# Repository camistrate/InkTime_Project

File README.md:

# TSC-homework - Istrate Camelia-Elena 334CC
# InkTime Watch

## Block Diagram

## Bill of Materials (BOM)

The table below lists the main active components, connectors, and critical electromechanical parts used in the design. Standard passives, RF matching parts, and decoupling capacitors are included in the manufacturing BOM.

| Component / Module | Function | Package / Footprint | JLC / LCSC Part | Datasheet |
|---|---|---|---|---|
| **nRF52840-QIAA-R** | Main BLE MCU | aQFN73 (7x7) | [C190794](https://jlcpcb.com/partdetail/NordicSemicon-NRF52840_QIAAR/C190794) | [Nordic nRF52840 Product Specification](https://docs.nordicsemi.com/) |
| **BQ25180YBGR** | LiPo charger / power-path management | DSBGA-9 | [C3682423](https://jlcpcb.com/partdetail/TexasInstruments-BQ25180YBGR/C3682423) | [TI BQ25180 Datasheet](https://www.ti.com/lit/ds/symlink/bq25180.pdf) |
| **RT6160AWSC** | 3.3V buck-boost regulator | WLCSP-15 | [C7065276](https://jlcpcb.com/partdetail/Richtek_Tech-RT6160AWSC/C7065276) | [Richtek RT6160A Datasheet](https://www.richtek.com/assets/product_file/RT6160A/DS6160A-05.pdf) |
| **MAX17048G+T10** | 1-cell LiPo fuel gauge | DFN-8 (2x2) | [C2682616](https://jlcpcb.com/partdetail/AnalogDevices-MAX17048G_T10/C2682616) | [MAX17048 / MAX17049 Datasheet](https://www.analog.com/media/en/technical-documentation/data-sheets/MAX17048-MAX17049.pdf) |
| **BMA421** | IMU / motion sensing / step counter | LGA-12 (2x2) | [C5242966](https://jlcpcb.com/partdetail/Bosch_Sensortec-BMA421/C5242966) | [Bosch BMA421 Datasheet](https://www.bosch-sensortec.com/media/boschsensortec/downloads/datasheets/bst-bma421-ds004.pdf) |
| **DRV2605YZFR** | Haptic driver for ERM motor | VSSOP-10 / DSBGA-9 variant used in sources | [C81079](https://jlcpcb.com/partdetail/TexasInstruments-DRV2605YZFR/C81079) | [TI DRV2605 Datasheet](https://www.ti.com/cn/lit/ds/symlink/drv2605.pdf) |
| **2450AT18B100E** | 2.4 GHz chip antenna | SMD 3216 / 1206 class | [C5179427](https://jlcpcb.com/partdetail/Johanson_Technology-2450AT18B100E/C5179427) | [Johanson 2450AT18B100E Datasheet](https://www.johansontechnology.com/datasheets/2450AT18B100/2450AT18B100.pdf) |
| **USBLC6-2SC6Y** | USB ESD protection | SOT-23-6 | [C7519](https://jlcpcb.com/partdetail/Stmicroelectronics-USBLC6_2SC6Y/C7519) | [ST USBLC6-2 Datasheet](https://www.st.com/resource/en/datasheet/usblc6-2.pdf) |
| **KH-TYPE-C-16P** | USB Type-C connector | 16-pin SMD | [C2765186](https://jlcpcb.com/partdetail/Kinghelm-KH_TYPE_C_16P/C2765186) | [Kinghelm KH-TYPE-C-16P Datasheet](https://datasheet.lcsc.com/lcsc/2012121836_Kinghelm-KH-TYPE-C-16P_C2765186.pdf) |
| **503480-2400** | 24-pin 0.5 mm FPC connector for E-paper display | 24-pin FPC | [C2857168](https://jlcpcb.com/partdetail/Molex-5034802400/C2857160) | [Molex 503480-2400 Datasheet](https://www.molex.com/en-us/products/part-detail/5034802400) |
| **DMG2305UX** | P-channel MOSFET for E-paper power control | SOT-23 | [C2940629](https://jlcpcb.com/partdetail/TECHPUBLIC-DMG2305UX/C2940629) | [DMG2305UX Datasheet](https://www.diodes.com/assets/Datasheets/DMG2305UX.pdf) |
| **SI1308EDL-T1-GE3** | MOSFET used in display drive stage | SOT-23 | [C469327](https://jlcpcb.com/partdetail/VishayIntertech-SI1308EDL_T1GE3/C469327) | [SI1308EDL Datasheet](https://www.vishay.com/doc?63399) |
| **MBR0530** | Schottky diode used in E-paper pump circuit | SOD-123 | [C77336](https://jlcpcb.com/partdetail/78464-MBR0530/C77336) | [MBR0530 Datasheet](https://www.onsemi.com/pdf/datasheet/mbr0530t1-d.pdf) |
| **EVP-AKE31A / tactile switch** | User input buttons | SMD tactile | [C2845028](https://jlcpcb.com/partdetail/Panasonic-EVP_AKE31A/C2845028) | [Panasonic Tactile Switch Datasheet](https://industrial.panasonic.com/cdbs/www-data/pdf/ATV0000/ATV0000CE3.pdf) |
| **LCM1027B3605F** | Vibration motor | Wire leads | [C7528806](https://jlcpcb.com/partdetail/7528806-LCM1027B3605F/C7528806) | [LCM1027B3605F Datasheet](https://datasheet.lcsc.com/lcsc/2310131633_LCM-LCM1027B3605F_C7528806.pdf) |
| **TC2030-IDC** | SWD programming / debug interface | Tag-Connect 6-pin footprint | [Tag-Connect Product Page](https://www.tag-connect.com/product/tc2030-idc-nl) | [TC2030 Documentation](https://www.tag-connect.com/product/tc2030-idc-6-pin-tag-connect-plug-of-nails-spring-pin-cable-with-ribbon-connector) |
| **32 MHz Crystal** | Main high-frequency crystal for nRF52840 | 2016 | [C5265841](https://jlcpcb.com/partdetail/Huiyuancrystal-HY32MSMD2016CA1R30/C5265841) | [32 MHz Crystal Datasheet](https://www.lcsc.com/product-detail/C7275071.html) |
| **32.768 kHz Crystal** | Low-frequency RTC crystal | 3215 | [C70509](https://jlcpcb.com/partdetail/NDK-NX3215SA_32_768KHZ_EXS00AMU00466/C70509) | [32.768 kHz Crystal Datasheet](https://ro.mouser.com/ProductDetail/NDK/NX3215SA-32.768K-STD-MUS-2) |
| **E-Paper Display 1.54 inch** | Main display module | 24-pin FPC | [C359944](https://jlcpcb.com/partdetail/Waveshare-4_2inch_e_PaperModule/C359944) | [WSH-12561 Datasheet](https://www.tme.eu/Document/0ca57a8ffbcd57b5bca53252eb9d6ec3/WSH-12561.pdf) |
| **LiPo Battery 250 mAh** | Main energy storage | Battery pack | - | [AKY0106 Datasheet](https://www.tme.eu/Document/b9e12bf26ad0ba929a22ab5d58f022cd/AKY0106.pdf) |

## Hardware Description

### MCU - nRF52840

The **nRF52840** is the central processing unit of the system. It integrates:

* ARM Cortex-M4F running at 64 MHz with FPU
* Bluetooth Low Energy (BLE 5.0)
* USB 2.0 Full Speed interface
* 1 MB Flash / 256 KB RAM

All major peripherals are connected directly to the nRF52840 through SPI, I2C, and GPIO interfaces.

---

## Power Path

```text
USB-C --> BQ25180 (charger) --> LiPo battery
                             --> VSYS
VSYS --> RT6160 (buck-boost) --> 3.3V rail (VDD_3V3)
```

### BQ25180

The **BQ25180** is used as the battery charger and power-path management IC. It:

* charges the LiPo battery
* provides the system rail (VSYS)
* communicates with the MCU over I2C
* raises an interrupt for charger or fault events

### RT6160

The **RT6160** is the main buck-boost regulator. It converts VSYS to a stable **3.3V rail**, which powers:

* the nRF52840
* the sensors
* the display logic
* the haptic driver

### MAX17048

The **MAX17048** is used as a fuel gauge. It monitors battery voltage and state of charge and communicates with the MCU over I2C. It also provides an **ALERT** signal for low-battery or battery-status events.

---

## E-Paper Display

The e-paper display is controlled through SPI and additional GPIO control signals.

| Signal   | Direction     | Description           |
| -------- | ------------- | --------------------- |
| SCK      | MCU → Display | SPI clock             |
| MOSI     | MCU → Display | SPI data              |
| EPD_CS   | MCU → Display | Chip select           |
| EPD_DC   | MCU → Display | Data / Command select |
| EPD_RST  | MCU → Display | Display reset         |
| EPD_BUSY | Display → MCU | Busy/status signal    |

The display power circuit includes:

* inductors
* Schottky diodes
* MOSFET switching elements

This stage generates the voltages required by the e-paper panel, such as **PREVGH** and **PREVGL**.

---

## IMU - BMA421

The **BMA421** is the motion sensor used in the design.

* Interface: **I2C**
* Functions:

  * acceleration sensing
  * motion detection
  * step-related events
* Interrupt outputs:

  * **INT1**
  * **INT2**

---

## Haptic Driver - DRV2605

The **DRV2605** is used to drive the vibration motor.

* Interface: **I2C**
* Enable signal: **HAPTIC_EN**
* Function: haptic feedback generation

---

## USB Interface

The board uses a **USB Type-C connector** together with an **USBLC6-2SC6Y** ESD protection device.

Signals:

* **VBUS**
* **D+**
* **D-**

This interface is used for:

* charging input
* USB detection by the MCU

---

## RF and Antenna

A **2450AT18B100E 2.4 GHz chip antenna** is connected to the RF output of the nRF52840.

The RF section includes:

* matching network components
* antenna keepout area
* no copper/traces under the antenna region

---

## User Interface

The design includes three push buttons:

* Up
* Down
* Enter / Esc

These are connected to GPIO pins of the MCU and used as active-low digital inputs.

---

## Debug Interface

Programming and debugging are performed through the **TC2030 SWD interface**, using:

* SWDIO
* SWDCLK
* RESET
* SWO
* 3.3V
* GND

---

## nRF52840 Pin Mapping

### Shared I2C Bus

* **P0.06** - SDA
  Used for communication with:

  * BMA421
  * MAX17048
  * BQ25180
  * RT6160
  * DRV2605

* **P0.07** - SCL
  Shared I2C clock line for all I2C peripherals

### SPI Bus (E-Paper Display)

* **P0.02** - SCK
* **P0.03** - MOSI
* **P0.05** - EPD_CS
* **P0.15** - EPD_DC
* **P0.16** - EPD_RST
* **P0.17** - EPD_BUSY

### Display Power Control

* **P1.01** - PFET gate control for display power enable

### Interrupts and Peripheral Control

* **P0.08** - BMA421 INT1
* **P1.08** - BMA421 INT2
* **P0.10** - MAX17048 ALERT
* **P0.11** - BQ25180 PMIC interrupt
* **P0.12** - DRV2605 enable

### Buttons

* **P0.13** - Up button
* **P0.14** - Down button
* **P1.00** - Enter / Esc button

### USB

* **D+** - USB data positive
* **D-** - USB data negative
* **VBUS** - USB power detection

### RF

* **ANT** - connected to the 2.4 GHz antenna through the matching network

### Debug and Clocks

* **SWDIO** - debug data
* **SWDCLK** - debug clock
* **RESET** - hardware reset
* **SWO** - debug trace output
* **XC1 / XC2** - 32 MHz crystal
* **XL1 / XL2** - 32.768 kHz crystal

---

## Design Rationale for Pin Selection

The selected pins were chosen to:

* use dedicated hardware interfaces for I2C and SPI
* keep related signals grouped logically
* simplify PCB routing
* support interrupt-driven operation for low-power behavior
* provide a clean debug and programming interface

---

## Power Consumption Considerations

The hardware is designed for low-power operation:

* **nRF52840** supports sleep and low-power modes
* **E-paper display** only consumes significant power during refresh
* **BMA421** is a low-power motion sensor
* **DRV2605 + motor** draw higher current only during short haptic events

Power efficiency is improved by:

* enabling only the peripherals that are needed
* using a regulated 3.3V rail
* controlling display-related power stages separately

## PCB Top View

## 3D PCB Render

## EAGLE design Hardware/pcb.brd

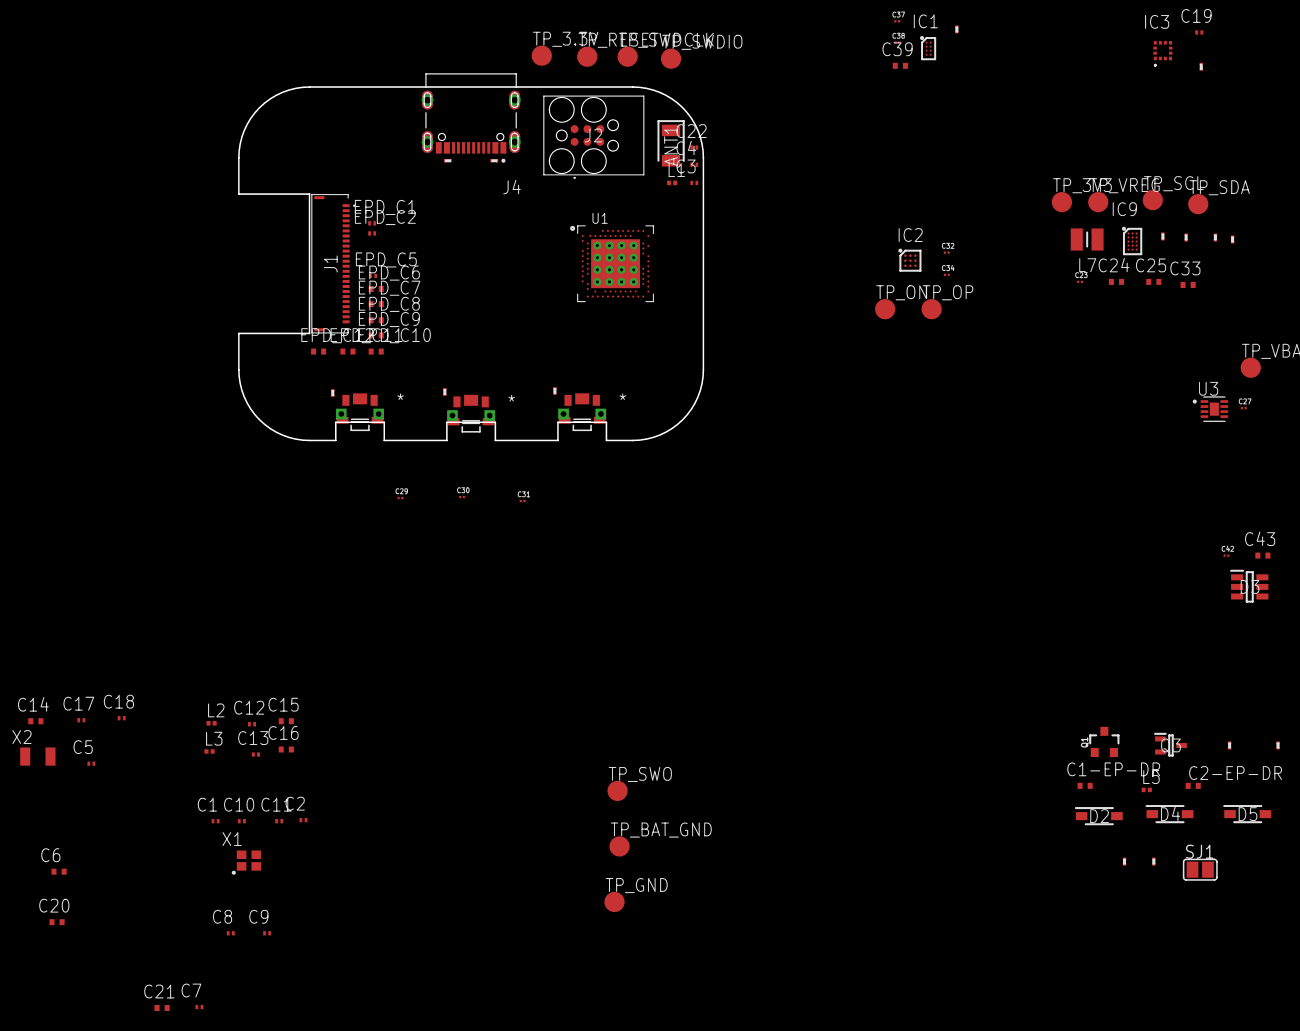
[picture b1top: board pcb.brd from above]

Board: 4 copper layers, 46.0 x 35.0 mm, 105 parts (0 on the bottom side), 75 nets, no tracks yet.

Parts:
ANT1: 2450AT18B100E; 2450AT18B100E_ANTC3216X140N
C1, C2, C17, C18: 12pF; NORDIC_NRF_3_RESC0201_L
C1-EP-DR, C24, C39: 10uF; NORDIC_NRF_3_RESC0402_L
C2-EP-DR: 4.7uF/25V; NORDIC_NRF_3_RESC0402_L
C3, C4: 1pF; NORDIC_NRF_3_RESC0201_L
C5, C7, C8, C12, C19: 100nF; NORDIC_NRF_3_RESC0201_L
C6, C14, C20, C21: 4.7µF; NORDIC_NRF_3_RESC0402_L
C9: 820pF; NORDIC_NRF_3_RESC0201_L
C10, C13, C22: N.C.; NORDIC_NRF_3_RESC0201_L
C11: 100pF; NORDIC_NRF_3_RESC0201_L
C15: 1.0µF; NORDIC_NRF_3_RESC0402_L
C16: 47µF; NORDIC_NRF_3_RESC0402_L
C23, C27, C34, C42: 0.1uF; GRM011R60J152KE01L_2_CAPC0201X13N
C25, C33: 22uF; NORDIC_NRF_3_RESC0402_L
C29, C30, C31, C32, C37, C38: 1uF; GRM011R60J152KE01L_2_CAPC0201X13N
C43: 4.7uF; NORDIC_NRF_3_RESC0402_L
D2, D4, D5: MBR0530; ESP32_C6_LIBRARY_5_SOD3716X135N
D3: USBLC6-2SC6Y; ESP32_C6_LIBRARY_3_SOT95P280X145-6N
EPD_C1, EPD_C2: 1uF/50V; NORDIC_NRF_3_RESC0201_L
EPD_C5: 0.1uF/50V; NORDIC_NRF_3_RESC0201_L
EPD_C6, EPD_C7, EPD_C8, EPD_C9, EPD_C10, EPD_C11, EPD_C12: 1uF/50V; NORDIC_NRF_3_RESC0402_L
IC1: BQ25180YBGR; BQ25180YBGR_BGA8C40P2X4_100X155X50
IC2: DRV2605YZFR; DRV2605YZFR_BGA9C50P3X3_144X144X62
IC3: BMA423; BMA423_BMA423
IC9: RT6160AWSC; RT6160AWSC_BGA15C40P3X5_140X230X60
J1: 503480-2400; 503480-2400_5034802400
J2: TC2030-IDC; TC2030-IDC_TC2030IDC
J4: KH-TYPE-C-16P; KH-TYPE-C-16P_KINGHELM_KH-TYPE-C-16P
L1: 3.9nH; NORDIC_NRF_2_RESC0201_N
L2: 10µH; NORDIC_NRF_2_RESC0201_N
L3: 15µH; NORDIC_NRF_2_RESC0201_N
L5: 68uH; NORDIC_NRF_2_RESC0201_N
L7: FTC252012SR47MBCA; MLP2016SR47MT0S1_INDC2016X100N
Q1: 20V/4.2A/52mΩ/1.4W; ESP32_C6_LIBRARY_4_ESP32_C6_LIBRARY_4_ESP32_C6_LIBRARY_4_ES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
Q3: SI1308EDL-T1-GE3; ESP32_C6_LIBRARY_6_SOT65P210X110-3N
R1_EP_DR: 0.47; CPF0201D7K68C1_0201
R1_USB, R2_USB: 5k1; ERA-1AEB3401C_0201
R2, R4: 0; CPF0201D7K68C1_0201
R2_EP_DR: 10K; CPF0201D7K68C1_0201
R3: 0; ERA-1AEB3401C_0201
R5, R7, R8, R9: 10k; CPF0201D7K68C1_0201
R17, R18: 3K3; ERA-1AEB3401C_0201
R_PWR_EPD: 10K; CPF0201D7K68C1_0201
R_TYPE_SEL: 2.2; CPF0201D7K68C1_0201
SJ1: ESP32_C6_LIBRARY_7_JUMPER_SJ
SW_DN: 2025-10-22_07-23-44_LIBRARY_EVP-AKE31ASW_EVP-AKE3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; 2025-10-22_07-23-44_LIBRARY_SW_EVP-AKE31A_PAN
SW_ENT: 2025-10-22_07-23-44_LIBRARY_EVP-AKE31ASW_EVP-AKE3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; 2025-10-22_07-23-44_LIBRARY_SW_EVP-AKE31A_PAN
SW_UP: 2025-10-22_07-23-44_LIBRARY_EVP-AKE31ASW_EVP-AKE3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; 2025-10-22_07-23-44_LIBRARY_SW_EVP-AKE31A_PAN
TP_3.3V, TP_3V3: HECTOR_WATCH_1_TPTP20R; HECTOR_WATCH_1_TP20R
TP_BAT_GND: HECTOR_WATCH_1_TPTP20R; HECTOR_WATCH_1_TP20R
TP_GND: HECTOR_WATCH_1_TPTP20R; HECTOR_WATCH_1_TP20R
TP_ON: HECTOR_WATCH_1_TPTP20R; HECTOR_WATCH_1_TP20R
TP_OP: HECTOR_WATCH_1_TPTP20R; HECTOR_WATCH_1_TP20R
TP_RESET: HECTOR_WATCH_1_TPTP20R; HECTOR_WATCH_1_TP20R
TP_SCL: HECTOR_WATCH_1_TPTP20R; HECTOR_WATCH_1_TP20R
TP_SDA: HECTOR_WATCH_1_TPTP20R; HECTOR_WATCH_1_TP20R
TP_SWDCLK: HECTOR_WATCH_1_TPTP20R; HECTOR_WATCH_1_TP20R
TP_SWDIO: HECTOR_WATCH_1_TPTP20R; HECTOR_WATCH_1_TP20R
TP_SWO: HECTOR_WATCH_1_TPTP20R; HECTOR_WATCH_1_TP20R
TP_VBAT: HECTOR_WATCH_1_TPTP20R; HECTOR_WATCH_1_TP20R
TP_VREG: HECTOR_WATCH_1_TPTP20R; HECTOR_WATCH_1_TP20R
U1: NRF52840_QF; NORDIC_NRF_4_AQFN50P700X700X85_HS-74N
U3: MAX17048G+T10; ESP32_C6_LIBRARY_SON50P200X200X80-9N
X1: 32MHz; NORDIC_NRF_BT-XTAL_2016_N
X2: 32.768kHz; NORDIC_NRF_1_XTAL_3215_N

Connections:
3V3/1.7D: C34.2, IC2.C2, Q1.2, R5.2, R_PWR_EPD.2
3V3/2.4A: C6.1, C7.1, C8.1, C12.1, C14.1, C19.1, C25.1, C33.1, IC3.3, IC3.7, IC3.10, IC9.E2, IC9.E3, J2.1, R17.1, R18.1, TP_3.3V.TP, TP_3V3.TP, U1.P$A22, U1.P$AD14, U1.P$AD23, U1.P$B1, U1.P$W1, U1.P$Y2
ALERT: U1.P$J24, U3.5
D+: D3.4, U1.P$AD6
D-: D3.6, U1.P$AD4
DEC1: C5.1, U1.P$C1
DEC3: C11.1, U1.P$D23
DEC4_6: C10.1, C15.1, C16.1, L3.2, U1.P$B5, U1.P$E24
DN: D3.1, J4.A7, J4.B7
DP: D3.3, J4.A6, J4.B6
EPD_3V3: C1-EP-DR.1, EPD_C5.2, J1.15, J1.16, L5.1, Q1.3
EPD_BUSY: J1.9, U1.P$AD12
EPD_CS: J1.12, U1.P$K2
EPD_DC: J1.11, U1.P$AD10
EPD_RST: J1.10, U1.P$AC11
GDR: J1.2, Q3.1, R2_EP_DR.2
GND: C1.2, C1-EP-DR.2, C2.2, C3.2, C4.2, C5.2, C6.2, C7.2, C8.2, C9.2, C10.2, C11.2, C12.2, C13.2, C14.2, C15.2, C16.2, C17.1, C18.1, C19.2, C20.2, C21.2, C22.2, C23.2, C24.1, C25.2, C27.1, C29.1, C30.1, C31.1, C32.1, C33.2, C34.1, C37.1, C38.1, C39.2, C42.2, C43.2, D3.2, D4.1, EPD_C1.1, EPD_C2.1, EPD_C5.1, EPD_C6.1, EPD_C7.1, EPD_C8.1, EPD_C9.1, EPD_C10.1, EPD_C11.1, EPD_C12.1, IC1.D2, IC2.B1, IC2.B3, IC3.8, IC3.9, IC9.B1, IC9.C1, IC9.C2, IC9.C3, J1.8, J1.17, J1.MP1, J1.MP2, J2.3, J2.5, J4.A1_B12, J4.A12_B1, J4.SH1, J4.SH2, J4.SH3, J4.SH4, R1_USB.1, R2_EP_DR.1, R2_USB.2, R3.1, R9.1, R_TYPE_SEL.1, SJ1.1, SW_DN.1, SW_ENT.1, SW_UP.1, TP_BAT_GND.TP, TP_GND.TP, U1.P$74, U1.P$75, U1.P$76, U1.P$77, U1.P$78, U1.P$79, U1.P$80, U1.P$81, U1.P$82, U1.P$83, U1.P$84, U1.P$85, U1.P$86, U1.P$87, U1.P$88, U1.P$89, U1.P$90, U1.P$B7, U1.P$F23, U3.1, U3.4, U3.6, U3.9, X1.2, X1.4
HAPTIC_EN: IC2.A1, U1.P$U1
IMU_INT1: IC3.5, U1.P$N1
IMU_INT2: IC3.6, U1.P$P2
LX1: IC9.B2, IC9.B3, L7.1
LX2: IC9.D2, IC9.D3, L7.2
MOSI: J1.14, U1.P$B13
unnamed: EPD_C7.2, J1.19
unnamed: IC9.D1, R4.2
unnamed: IC1.D1, R9.2
unnamed: C20.1, U1.P$AC5
unnamed: IC9.E1, R2.2
unnamed: IC3.1, R3.2
unnamed: C2-EP-DR.1, D2.1, D4.2
unnamed: C2-EP-DR.2, D5.2, L5.2, Q3.3
unnamed: R1_EP_DR.1, R_TYPE_SEL.2, SJ1.2
unnamed: L2.1, U1.P$B3
unnamed: L2.2, L3.1
unnamed: C13.1, U1.P$A18
unnamed: C9.1, U1.P$N24
unnamed: C2.1, U1.P$A23, X1.3
unnamed: C3.1, L1.1, U1.P$H23
unnamed: C1.1, U1.P$B24, X1.1
unnamed: EPD_C2.2, J1.4
unnamed: EPD_C1.2, J1.5
unnamed: EPD_C12.2, J1.24
unnamed: EPD_C8.2, J1.20
unnamed: EPD_C10.2, J1.22
unnamed: EPD_C6.2, J1.18
unnamed: C32.2, IC2.A2
unnamed: J4.B5, R2_USB.1
unnamed: J4.A5, R1_USB.2
OUT+: IC2.A3, TP_OP.TP
OUT-: IC2.C3, TP_ON.TP
P0.00/XL1: C17.2, U1.P$D2, X2.1
P0.01/XL2: C18.2, U1.P$F2, X2.2
P0.13: C30.2, R5.1, SW_UP.2, U1.P$AD8
P0.14: C31.2, R8.1, SW_ENT.2, U1.P$AC9
P1.01: Q1.1, R_PWR_EPD.1, U1.P$Y23
P1.02: C29.2, R7.1, SW_DN.2, U1.P$W24
PMIC_INT: IC1.A1, U1.P$T2
PREVGH: D5.1, EPD_C9.2, J1.21
PREVGL: D2.2, EPD_C11.2, J1.23
RESE: J1.3, Q3.2, R1_EP_DR.2
RESET: J2.6, TP_RESET.TP, U1.P$AC13
RF: ANT1.1, C4.1, C22.1, L1.2
SCK: J1.13, U1.P$A12
SCL/1.4C: IC2.C1, U3.7
SCL/2.4C: IC1.B1, IC3.12, R4.1, R17.2, TP_SCL.TP, U1.P$M2
SDA/1.4C: IC2.B2, U3.8
SDA/2.4C: IC1.C1, IC3.2, R2.1, R18.2, TP_SDA.TP, U1.P$L1
SWDCLK: J2.4, TP_SWDCLK.TP, U1.P$AA24
SWDIO: J2.2, TP_SWDIO.TP, U1.P$AC24
SWO: TP_SWO.TP, U1.P$AD22
VBAT/1.2A: C27.2, TP_VBAT.TP, U3.2, U3.3
VBAT/2.5C: C37.2, IC1.C2
VBUS/1.5D: C42.1, C43.1, D3.5, J4.A4_B9, J4.A9_B4
VBUS/2.6D: C21.1, C38.2, IC1.A2, U1.P$AD2
VREG: C23.1, C24.2, C39.1, IC1.B2, IC9.A1, IC9.A2, IC9.A3, TP_VREG.TP

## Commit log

2026-04-10 Add Apache License 2.0
    Added Apache License 2.0 to the project.
2026-04-10 Added files
2026-04-21 Add block diagram to README
2026-04-21 Expand hardware description in README.md
    Added detailed hardware descriptions for components
2026-04-21 Add Bill of Materials section to README
    Added a Bill of Materials (BOM) section detailing components used in the design, including links to datasheets.
2026-04-21 Update README with PCB views and 3D render
    Added sections for PCB Top View and 3D PCB Render.
2026-04-21 New pcb img
2026-04-21 New files added
2026-04-21 Exploded updated

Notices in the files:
parts and their libraries:
COPYRIGHT: Copyright (C) 2025 Ultra Librarian. All rights reserved.
